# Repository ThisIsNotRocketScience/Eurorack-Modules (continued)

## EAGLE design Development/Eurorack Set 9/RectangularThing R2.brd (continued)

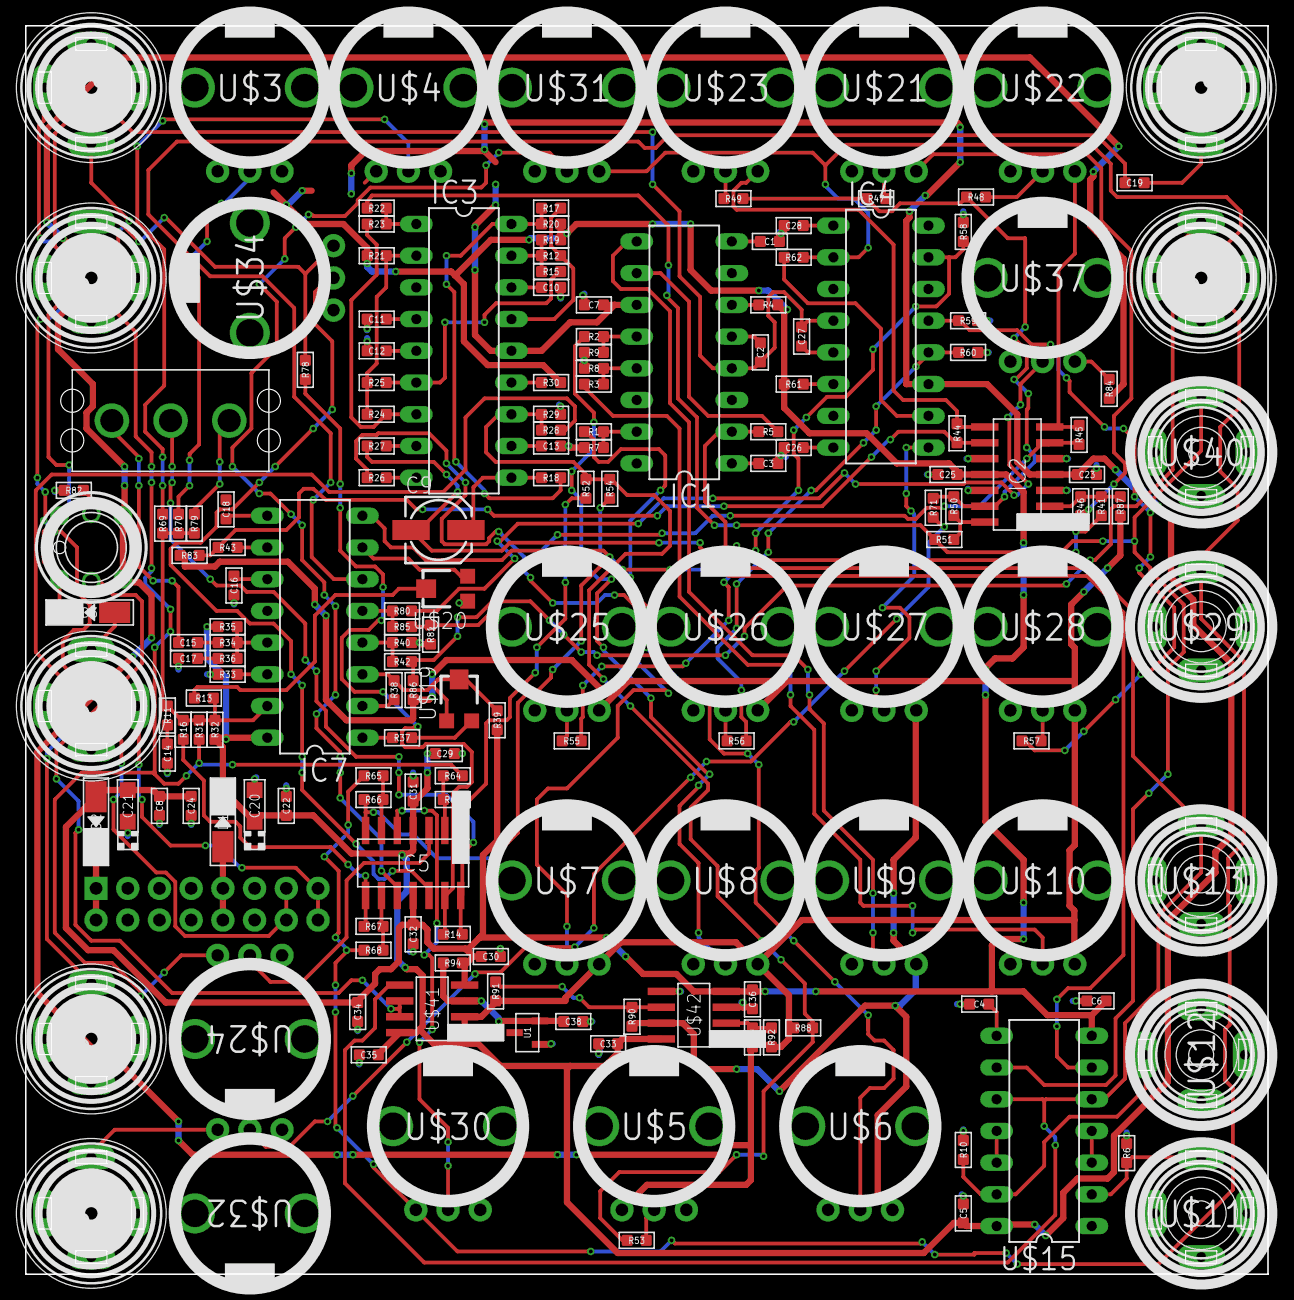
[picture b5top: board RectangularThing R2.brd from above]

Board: 2 copper layers, 99.5 x 100.0 mm, 176 parts (1 on the bottom side), 123 nets.

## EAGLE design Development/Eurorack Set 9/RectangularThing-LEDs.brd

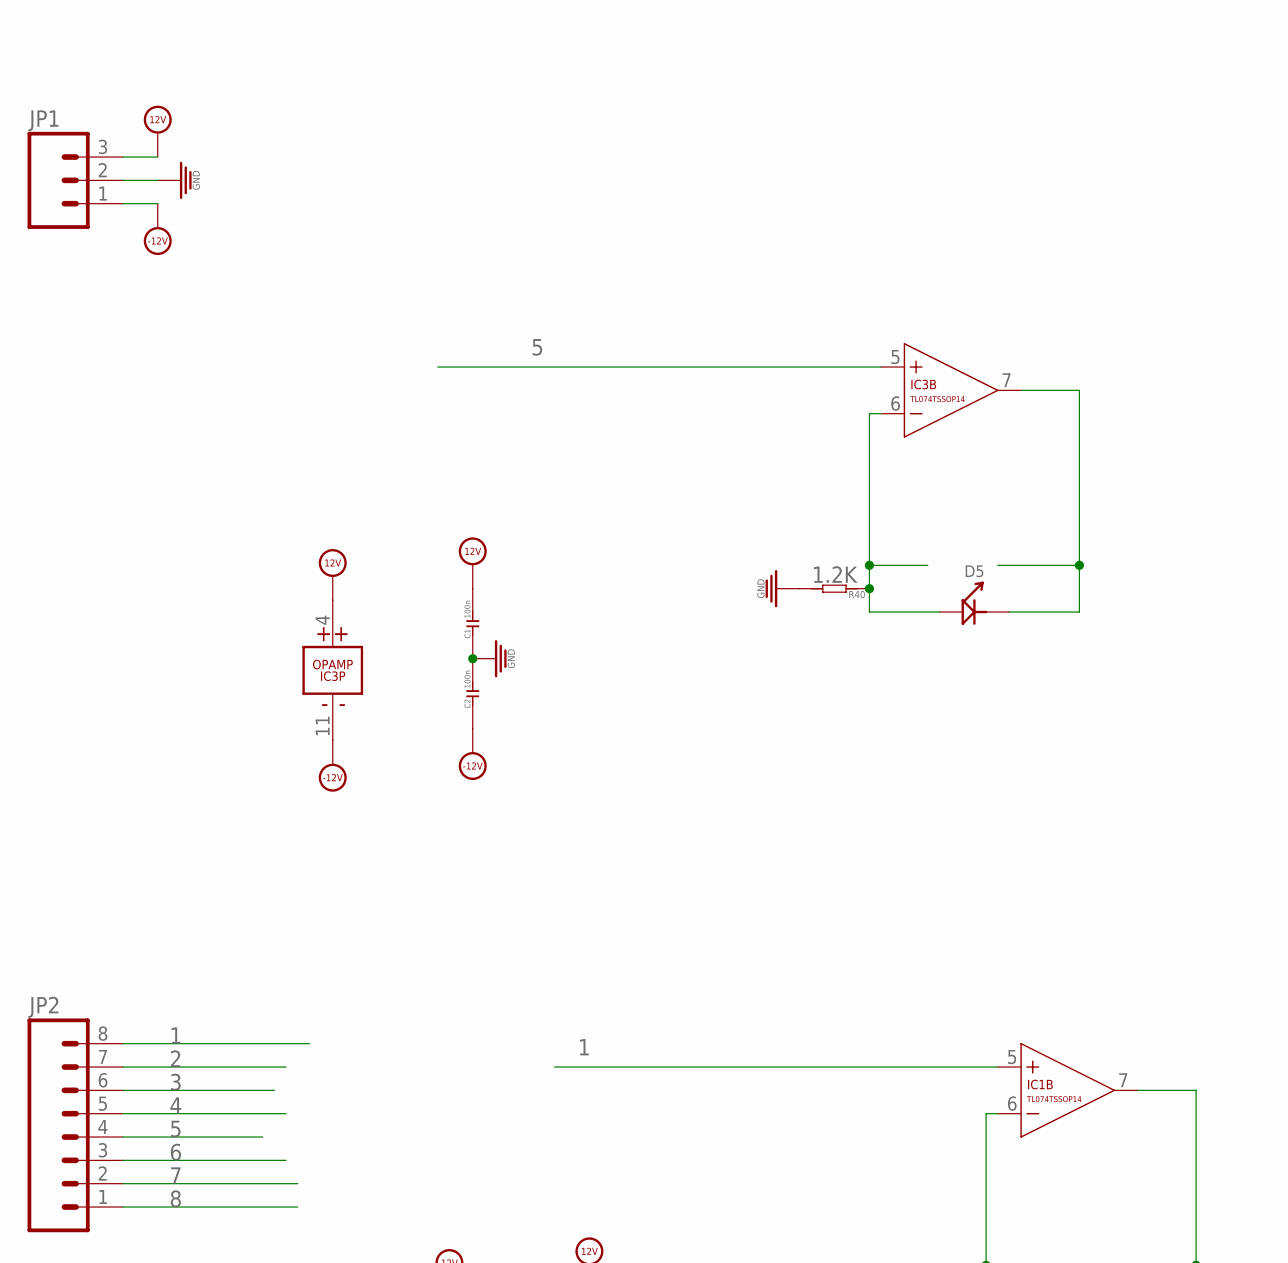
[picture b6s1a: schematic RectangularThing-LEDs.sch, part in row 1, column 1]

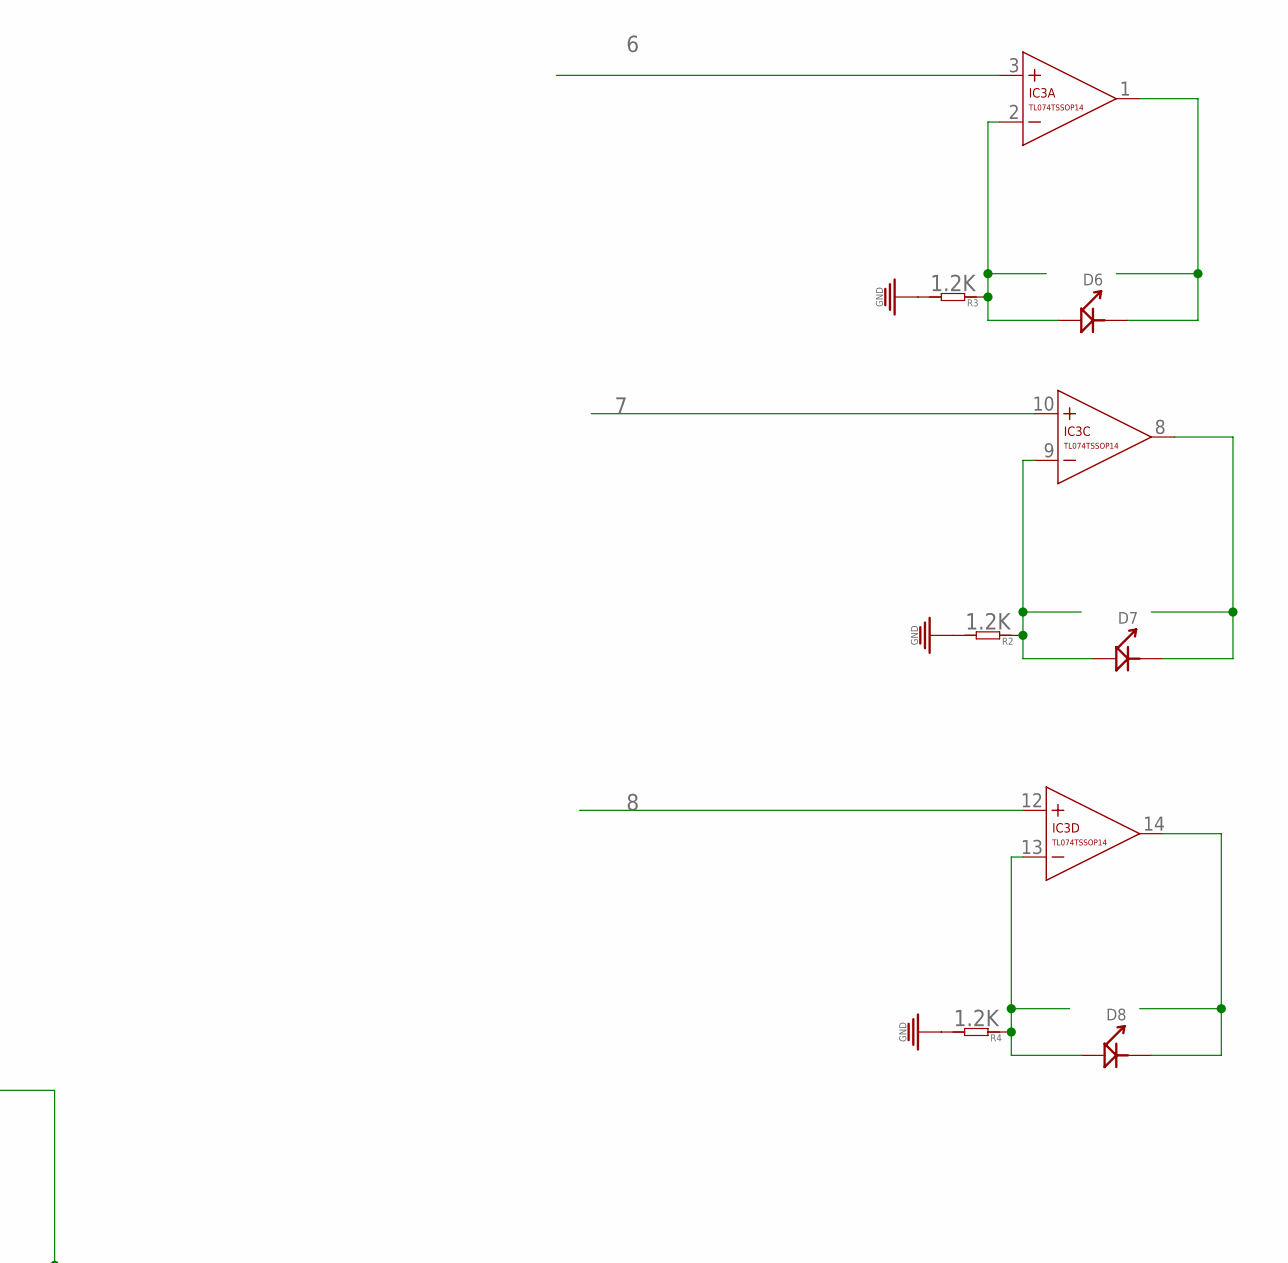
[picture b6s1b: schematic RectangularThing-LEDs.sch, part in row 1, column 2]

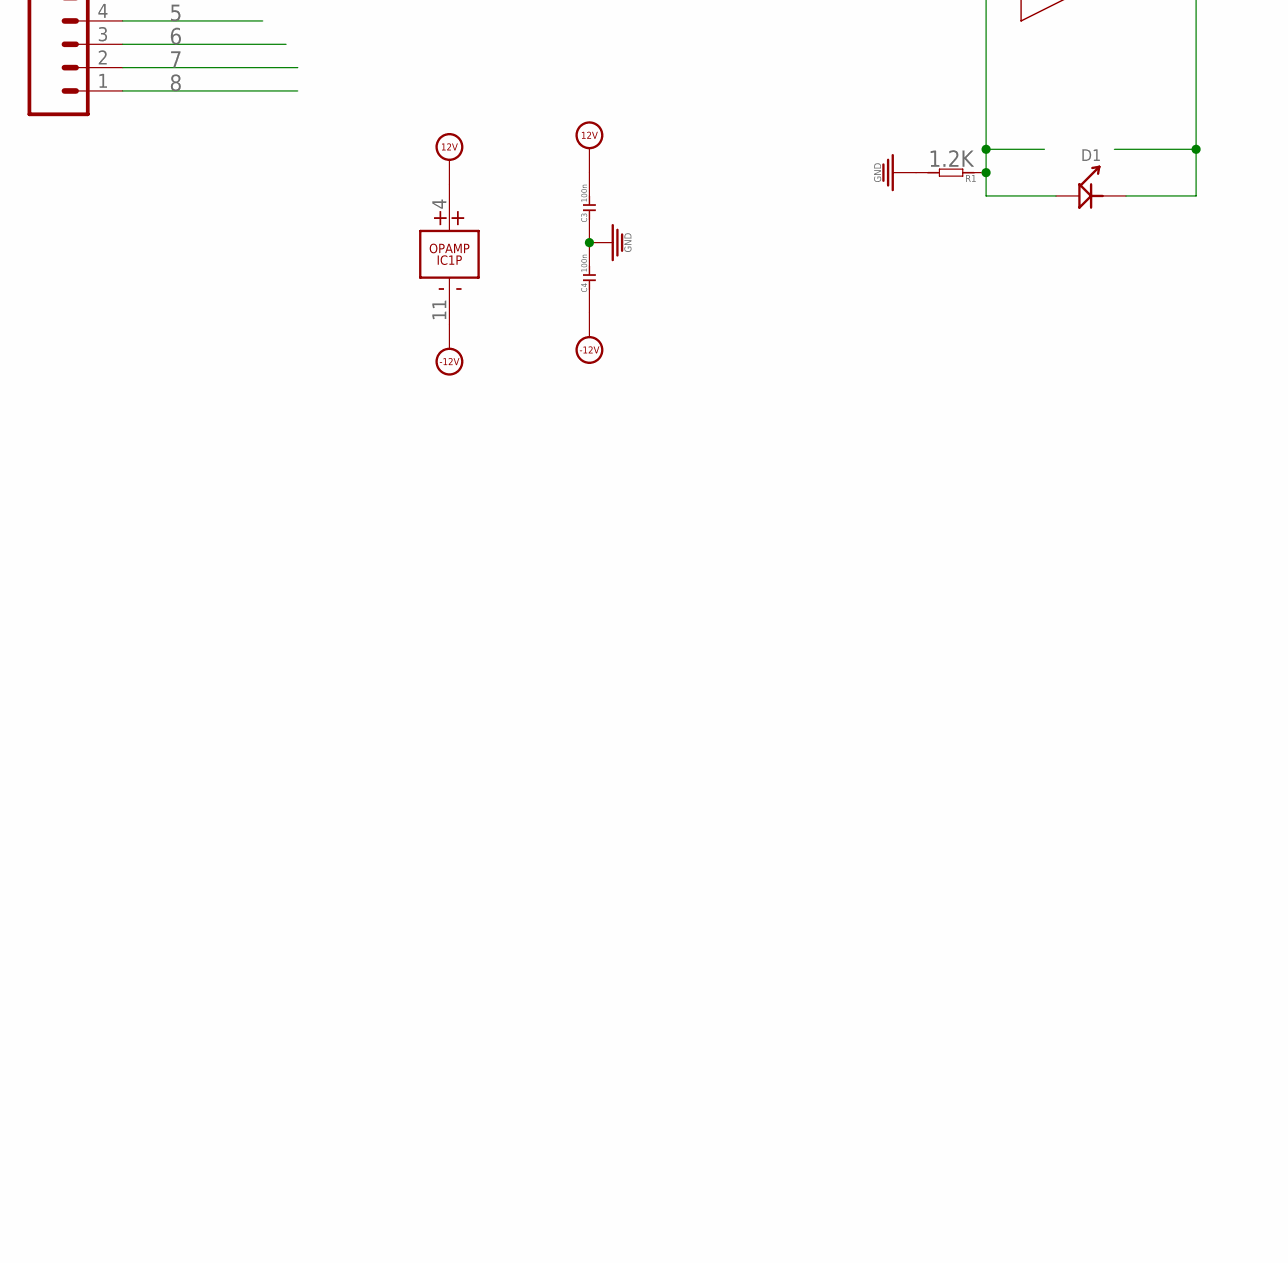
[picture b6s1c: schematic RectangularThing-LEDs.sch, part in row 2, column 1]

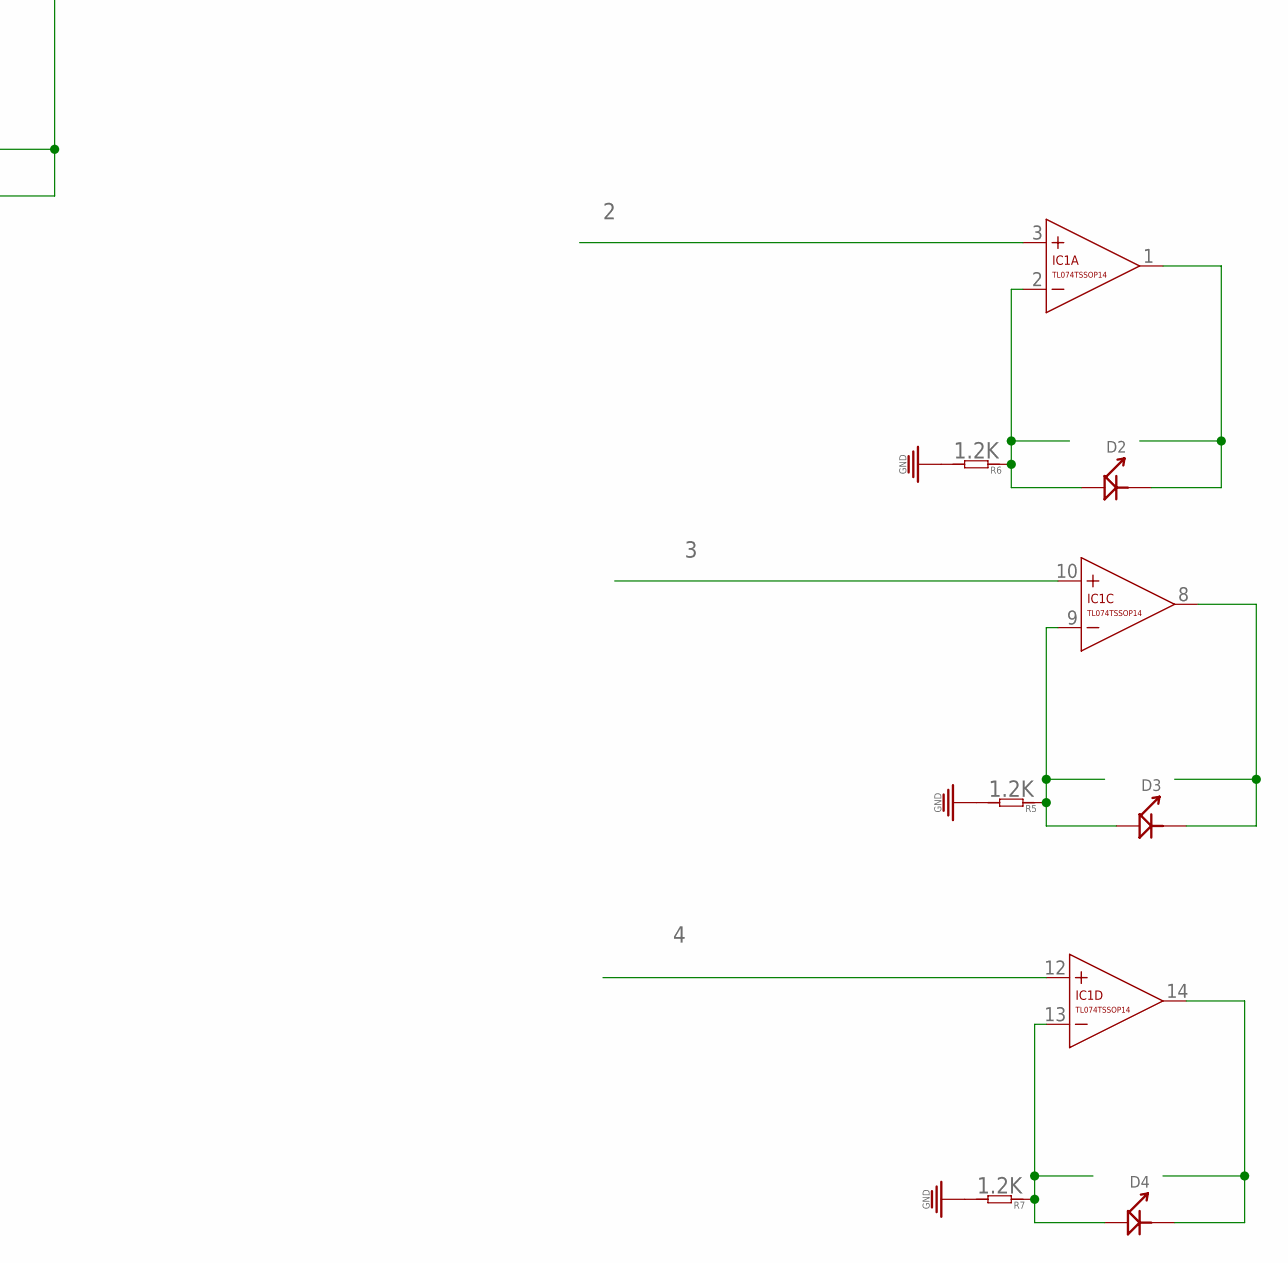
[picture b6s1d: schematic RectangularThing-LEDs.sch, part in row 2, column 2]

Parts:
C1, C2, C3, C4: 100n; C0603
D1, D2, D3, D4, D5, D6, D7, D8: LED; LED0603
IC1, IC3: TL074TSSOP14; TSSOP14
JP1: M03PTH; 1X03
JP2: M08LONGPADS; 1X08_LONGPADS
R1, R2, R3, R4, R5, R6, R7, R40: 1.2K; R0603

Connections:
1: IC1.5 (+IN), JP2.8
2: IC1.3 (+IN), JP2.7
3: IC1.10 (+IN), JP2.6
4: IC1.12 (+IN), JP2.5
5: IC3.5 (+IN), JP2.4
6: IC3.3 (+IN), JP2.3
7: IC3.10 (+IN), JP2.2
8: IC3.12 (+IN), JP2.1
12V: C1.2, C3.2, IC1.4 (V+), IC3.4 (V+), JP1.3
-12V: C2.1, C4.1, IC1.11 (V-), IC3.11 (V-), JP1.1
GND: C1.1, C2.2, C3.1, C4.2, JP1.2, R1.2, R2.2, R3.2, R4.2, R5.2, R6.2, R7.2, R40.2
unnamed: D1.+, IC1.6 (-IN), R1.1
unnamed: D1.-, IC1.7 (OUT)
unnamed: D7.+, IC3.9 (-IN), R2.1
unnamed: D7.-, IC3.8 (OUT)
unnamed: D6.+, IC3.2 (-IN), R3.1
unnamed: D6.-, IC3.1 (OUT)
unnamed: D8.+, IC3.13 (-IN), R4.1
unnamed: D8.-, IC3.14 (OUT)
unnamed: D3.+, IC1.9 (-IN), R5.1
unnamed: D3.-, IC1.8 (OUT)
unnamed: D2.+, IC1.2 (-IN), R6.1
unnamed: D2.-, IC1.1 (OUT)
unnamed: D4.+, IC1.13 (-IN), R7.1
unnamed: D4.-, IC1.14 (OUT)
unnamed: D5.+, IC3.6 (-IN), R40.1
unnamed: D5.-, IC3.7 (OUT)

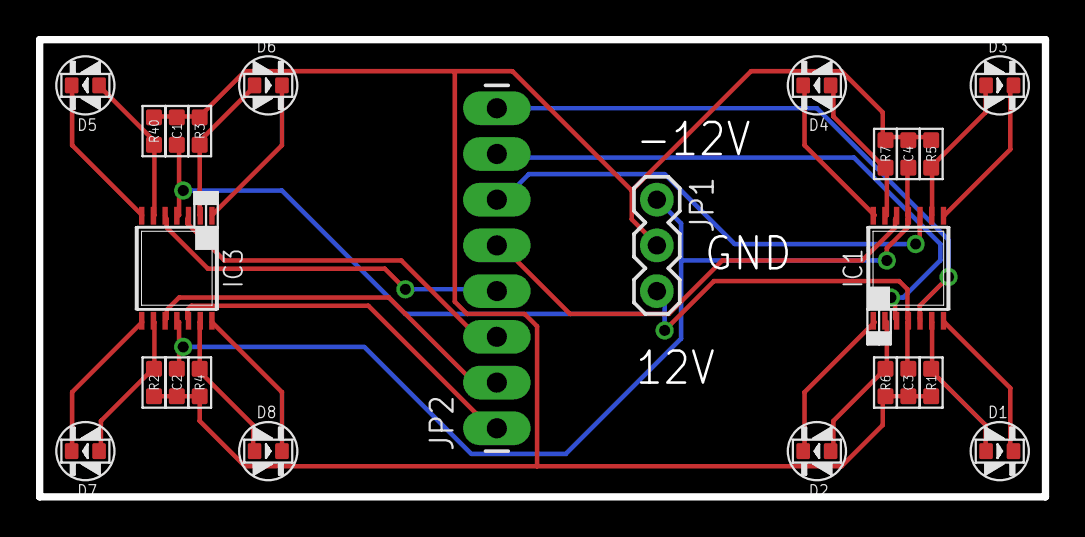
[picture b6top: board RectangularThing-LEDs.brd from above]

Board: 2 copper layers, 55.9 x 25.4 mm, 24 parts (0 on the bottom side), 27 nets.
